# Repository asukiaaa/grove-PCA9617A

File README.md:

# grove-PCA9617A

A PCB which transports I2C signal on grove cable through PCA9617A I2C releater.

## License

MIT

## References

- [PCA9617A](https://www.nxp.jp/docs/en/data-sheet/PCA9617A.pdf)

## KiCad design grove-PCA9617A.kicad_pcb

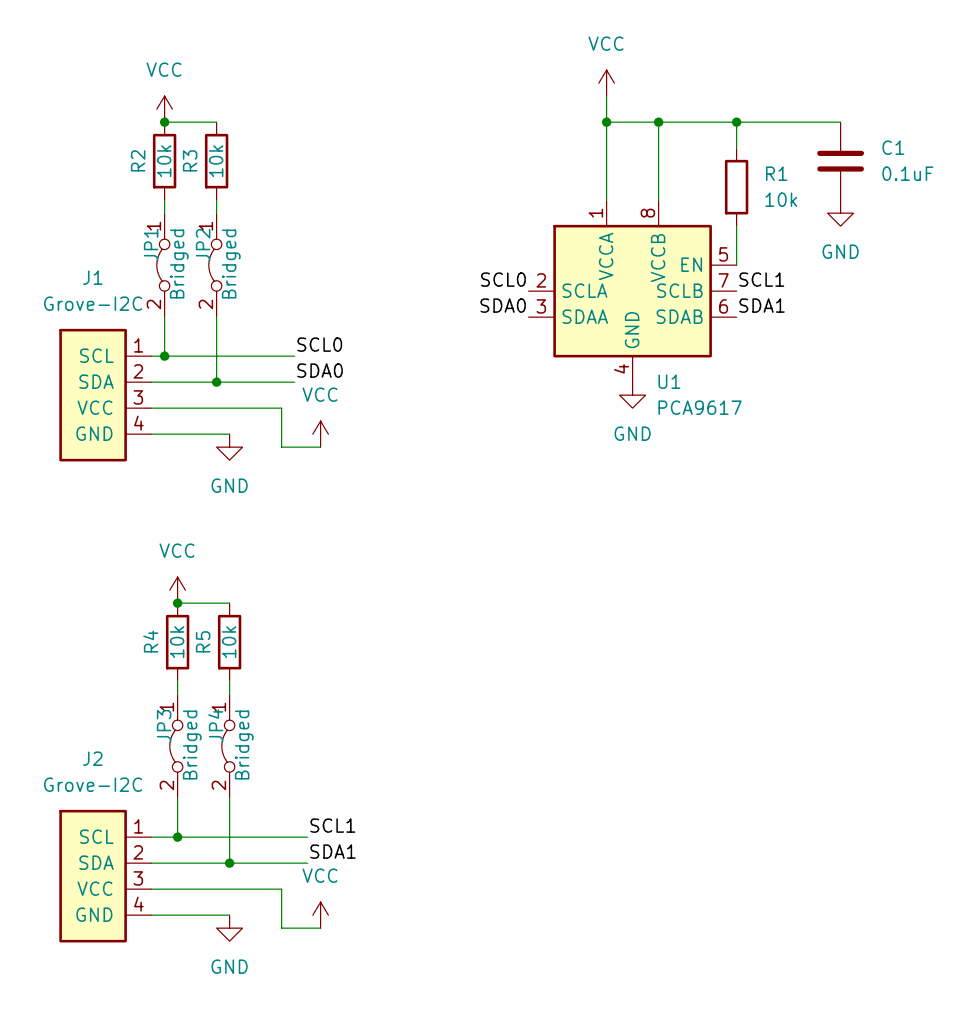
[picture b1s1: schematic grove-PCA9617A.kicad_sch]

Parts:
C1: 0.1uF; C_0402_1005Metric
J1, J2: Grove-I2C; NS-Tech_Grove_1x04_P2mm_Horizontal_silk_inside
JP1, JP2, JP3, JP4: Bridged; SolderJumper-2_P1.3mm_Bridged_RoundedPad1.0x1.5mm
R1, R2, R3, R4, R5: 10k; R_0402_1005Metric
U1: PCA9617; TSSOP-8_3x3mm_P0.65mm

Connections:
/SCL0: J1.1 (SCL), JP1.2 (B), U1.2 (SCLA)
/SCL1: J2.1 (SCL), JP3.2 (B), U1.7 (SCLB)
/SDA0: J1.2 (SDA), JP2.2 (B), U1.3 (SDAA)
/SDA1: J2.2 (SDA), JP4.2 (B), U1.6 (SDAB)
GND: C1.2, J1.4 (GND), J2.4 (GND), U1.4 (GND)
unnamed: JP1.1 (A), R2.2
unnamed: JP2.1 (A), R3.2
unnamed: JP3.1 (A), R4.2
unnamed: JP4.1 (A), R5.2
unnamed: R1.2, U1.5 (EN)
VCC: C1.1, J1.3 (VCC), J2.3 (VCC), R1.1, R2.1, R3.1, R4.1, R5.1, U1.1 (VCCA), U1.8 (VCCB)

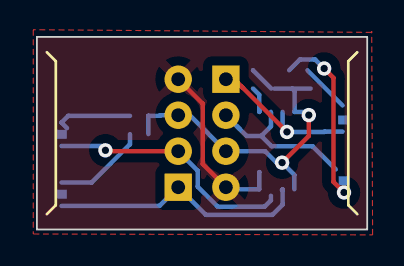
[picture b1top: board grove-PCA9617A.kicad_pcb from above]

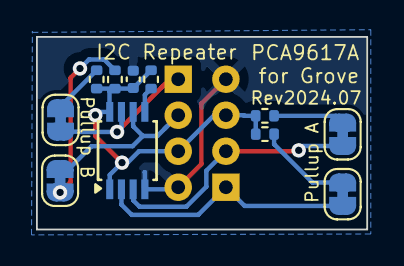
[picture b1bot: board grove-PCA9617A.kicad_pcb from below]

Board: 2 copper layers, 18.4 x 10.7 mm, 13 parts (11 on the bottom side), 11 nets.

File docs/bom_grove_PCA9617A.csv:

*Reference,*Manufacturer Part number,*QTY,*Original,Description,Purchase Link
U1,PCA9617ADPJ,1,Y,,https://www.digikey.jp/ja/products/detail/nxp-usa-inc/PCA961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
"R1,R2,R3,R4,R5",,5,N,10K 0402,
C1,,1,N,0.1uf 0402 more or eq 6V,
"J1,J2",,2,N,Grove connector horizontal THT,https://www.seeedstudio.com/Grove-Universal-4-pin-connector-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

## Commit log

2024-06-24 Add pullup resistors
2024-07-28 Update for KiCad8
2024-07-28 Add schema of rev2024.07
